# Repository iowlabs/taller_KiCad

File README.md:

# taller_KiCad
Archivos KiCad para la actividad del taller de KiCad realizado por iowLabs

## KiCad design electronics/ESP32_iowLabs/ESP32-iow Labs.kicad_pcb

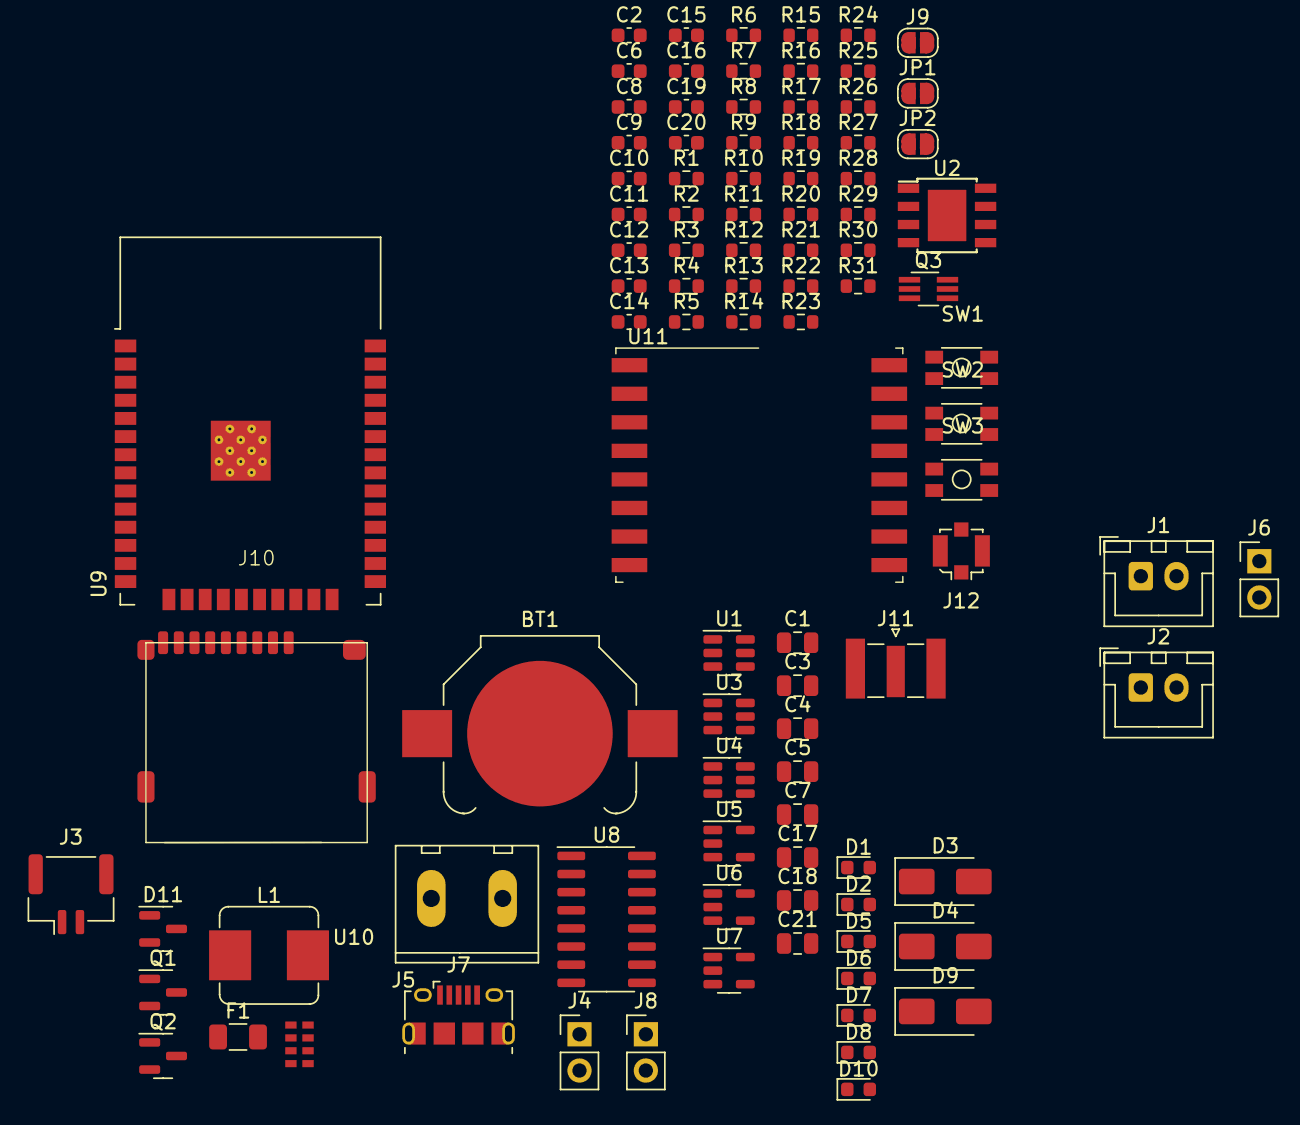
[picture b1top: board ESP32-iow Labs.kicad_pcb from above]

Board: 2 copper layers, 101 parts (0 on the bottom side), 61 nets, no tracks yet.

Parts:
BT1: Battery_Cell; BatteryHolder_Keystone_3000_1x12mm
C1, C5: 22u; C_0805_2012Metric
C2, C13, C14, C15, C16, C20: 100n; C_0603_1608Metric
C3, C4, C17, C18: 10u; C_0805_2012Metric
C6, C8, C9, C10, C11, C12: 1u; C_0603_1608Metric
C7, C21: 4.7u; C_0805_2012Metric
C19: 10n; C_0603_1608Metric
D1, D2, D5, D6, D7, D8, D10: LED; LED_0603_1608Metric
D3, D4, D9: D_Schottky; D_SMA
D11: BAS70-05; SOT-23
F1: FUSE; Fuse_1206_3216Metric
H1, H2, H3, H4: MountingHole; MountingHole_3.2mm_M3
J1: ON OFF; JST_XH_B2B-XH-A_1x02_P2.50mm_Vertical
J2: V_USB; JST_XH_B2B-XH-A_1x02_P2.50mm_Vertical
J3: BAT; JST_GH_BM02B-GHS-TBT_1x02-1MP_P1.25mm_Vertical
J4, J8: HDR-2x1; PinHeader_1x02_P2.54mm_Vertical
J5: IN; Tb-2x1-5p-TH-V
J6: ON OFF; PinHeader_1x02_P2.54mm_Vertical
J7: USB_B_Micro; USB_Micro-B_Amphenol_10118194_Horizontal
J9: Conn_01x02; SolderJumper-2_P1.3mm_Open_RoundedPad1.0x1.5mm
J10: microSD_push_push
J11: Conn_Coaxial; SMA_Samtec_SMA-J-P-X-ST-EM1_EdgeMount
J12: Conn_Coaxial; U.FL_Molex_MCRF_73412-0110_Vertical
JP1, JP2: SolderJumper_2_Open; SolderJumper-2_P1.3mm_Open_RoundedPad1.0x1.5mm
L1: 22u; L_Bourns_SRP7028A_7.3x6.6mm
Q1, Q2: Q_PMOS_GSD; SOT-23
Q3: Q_Dual_NPN_NPN_BRT_E1B1C2E2B2C1; SOT-363_SC-70-6_Handsoldering
R1, R11, R12, R13: 1k; R_0603_1608Metric
R2, R14, R15, R18, R19, R20: 10K; R_0603_1608Metric
R3: 100; R_0603_1608Metric
R4: 1K2; R_0603_1608Metric
R5, R7: 1K; R_0603_1608Metric
R6: 7K5; R_0603_1608Metric
R8: 12K; R_0603_1608Metric
R9: 470; R_0603_1608Metric
R10: 30K; R_0603_1608Metric
R16, R17: 200; R_0603_1608Metric
R21: 330; R_0603_1608Metric
R22, R23, R24, R25, R26: 3.3k; R_0603_1608Metric
R27, R28: 100k; R_0603_1608Metric
R29, R30: 2.2k; R_0603_1608Metric
R31: 10k; R_0603_1608Metric
SW1, SW2, SW3: SW_DIP_x02; SMD_SWITCH
U1: DW01; SOT-23-6
U2: TP4056; TP4056_SOP-8-PP
U3: MT3608; SOT-23-6
U4: FS8205A; SOT-23-6
U5, U6, U7: AP2112K-3.3; SOT-23-5
U8: CH340C; SOIC-16_3.9x9.9mm_P1.27mm
U9: ESP32-WROOM-32D; ESP32-WROOM-32
U10: RV-8803; SON-8
U11: RFM95W-915S2; HOPERF_RFM69HW

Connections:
+3V3: C8.1, C13.1, C16.1, C17.1, C21.2, R11.1, R18.1, R20.1, R31.1, U5.5 (VOUT), U8.4 (V3), U8.16 (VCC), U9.2 (VDD), U11.13 (3.3V)
+5V: C6.1, C9.1, C11.1, J4.1, J6.1, U5.1 (VIN), U5.3 (EN), U6.1 (VIN), U7.1 (VIN)
/BAT+: C3.1, J3.1, Q1.3 (D), R3.1, R8.2, U2.5 (BAT)
/BAT-: C2.2, J3.2, SW1.3, SW1.4, U1.6 (GND), U4.1 (S1)
/BAT_LVL: R8.1, R10.1, U9.7 (IO35)
/CS: R5.2, U1.2 (CS)
/C/D: J8.1, J10.9 (Cd)
/DTR#: Q3.4 (E1), R15.1, U8.13 (~DTR)
/Dat3: J8.2, J10.2 (CD/Dat3), R26.2
/EVI: J9.1, R28.2, U10.7 (EVI)
/FB_5V: R6.2, R7.1, U3.3 (FB)
/INT: R27.2, U10.6 (!INT)
/IO0: C14.1, Q3.3 (C1), R16.1, R18.2, U9.25 (IO0)
/IO2: R21.1, U9.24 (IO2)
/OC: U1.3 (OC), U4.4 (G2)
/OD: U1.1 (OD), U4.6 (G1)
/RESET: C15.1, Q3.6 (C1), R17.1, R20.2, U9.3 (EN)
/RST#: Q3.1 (E1), R19.2, U8.14 (~RTS)
/RX: U8.2 (TXD), U9.34 (RXD0/IO3)
/SCL: R29.2, U10.8 (SCL)
/SDA: R30.2, U10.1 (SDA)
/SW_5V: D3.2 (A), L1.2, U3.1 (SW)
/TX: U8.3 (RXD), U9.35 (TXD0/IO1)
/V1: C1.1, J1.1, L1.1, U3.4 (EN), U3.5 (IN)
/VDL_3V3: C10.1, C18.1, C20.1, D11.1 (A), D11.2 (A), J10.4 (VDD), R12.1, R27.1, R28.1, R29.1, R30.1, U6.5 (VOUT)
/VIN_5V: C7.1, J5.2, Q2.3 (D)
/VS_3V3: C12.1, R13.1, U7.5 (VOUT)
/V_USB: C4.1, D4.2 (A), D9.2 (A), F1.2, J2.1, Q1.1 (G), Q2.1 (G), R1.1, R2.1, R14.1, U2.4 (Vcc), U2.8 (CE)
/V_in: F1.1, J7.1 (VBUS)
/Vo_DCDC: C5.1, D3.1 (K), J4.2, R6.1, R9.1
/rfm_rst: R31.2, U11.6 (RESET)
/spi_clk: R24.1, U11.4 (SCK)
/spi_miso: R22.1, U11.2 (MISO)
/spi_mosi: R25.1, U11.3 (MOSI)
GND: BT1.2 (-), C1.2, C3.2, C4.2, C5.2, C6.2, C7.2, C8.2, C9.2, C10.2, C11.2, C12.2, C13.2, C14.2, C15.2, C16.2, C17.2, C18.2, C19.2, C20.2, C21.1, D5.1 (K), D6.1 (K), D7.1 (K), D8.1 (K), D10.1 (K), J2.2, J5.1, J7.5 (GND), J7.6 (Shield), J9.2, J10.6 (VSS), J10.10 (GND), J11.2 (Ext), J12.2 (Ext), R2.2, R4.1, R5.1, R7.2, R10.2, R14.2, SW1.1, SW1.2, SW2.1, SW2.2, SW3.1, SW3.2, U2.1 (TEMP), U2.3 (GND), U3.2 (GND), U4.3 (S2), U5.2 (GND), U6.2 (GND), U7.2 (GND), U8.1 (GND), U9.1 (GND), U9.15 (GND), U9.38 (GND), U9.39 (GND), U10.4 (CLKOE), U10.5 (VSS), U11.1 (GND), U11.8 (GND), U11.10 (GND)
unnamed: BT1.1 (+), R23.2
unnamed: D1.2 (A), D2.2 (A), R1.2
unnamed: D1.1 (K), U2.7 (~CHRG)
unnamed: D2.1 (K), U2.6 (~STDBY)
unnamed: D4.1 (K), J1.2, Q1.2 (S)
unnamed: D5.2 (A), R9.2
unnamed: D6.2 (A), R11.2
unnamed: D7.2 (A), R12.2
unnamed: D8.2 (A), R13.2
unnamed: D9.1 (K), J6.2, Q2.2 (S)
unnamed: D10.2 (A), R21.2
unnamed: C19.1, D11.3 (K), R23.1, U10.3 (VDD)
unnamed: J7.3 (D+), U8.5 (UD+)
unnamed: J7.2 (D-), U8.6 (UD-)
unnamed: J10.5 (CLK), R24.2
unnamed: J10.3 (CMD), R25.2
unnamed: J10.7 (Dat0), R22.2
unnamed: J11.1 (In), JP1.1 (A)
unnamed: J12.1 (In), JP2.1 (A)
unnamed: JP1.2 (B), JP2.2 (B), U11.9 (ANT)
unnamed: Q3.5 (B1), R19.1
unnamed: Q3.2 (B1), R15.2
unnamed: R16.2, SW2.3, SW2.4
unnamed: R17.2, SW3.3, SW3.4
unnamed: C2.1, R3.2, U1.5 (VCC)
unnamed: R4.2, U2.2 (PROG)

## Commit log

2024-08-04 adding example
2024-08-04 fixing links
